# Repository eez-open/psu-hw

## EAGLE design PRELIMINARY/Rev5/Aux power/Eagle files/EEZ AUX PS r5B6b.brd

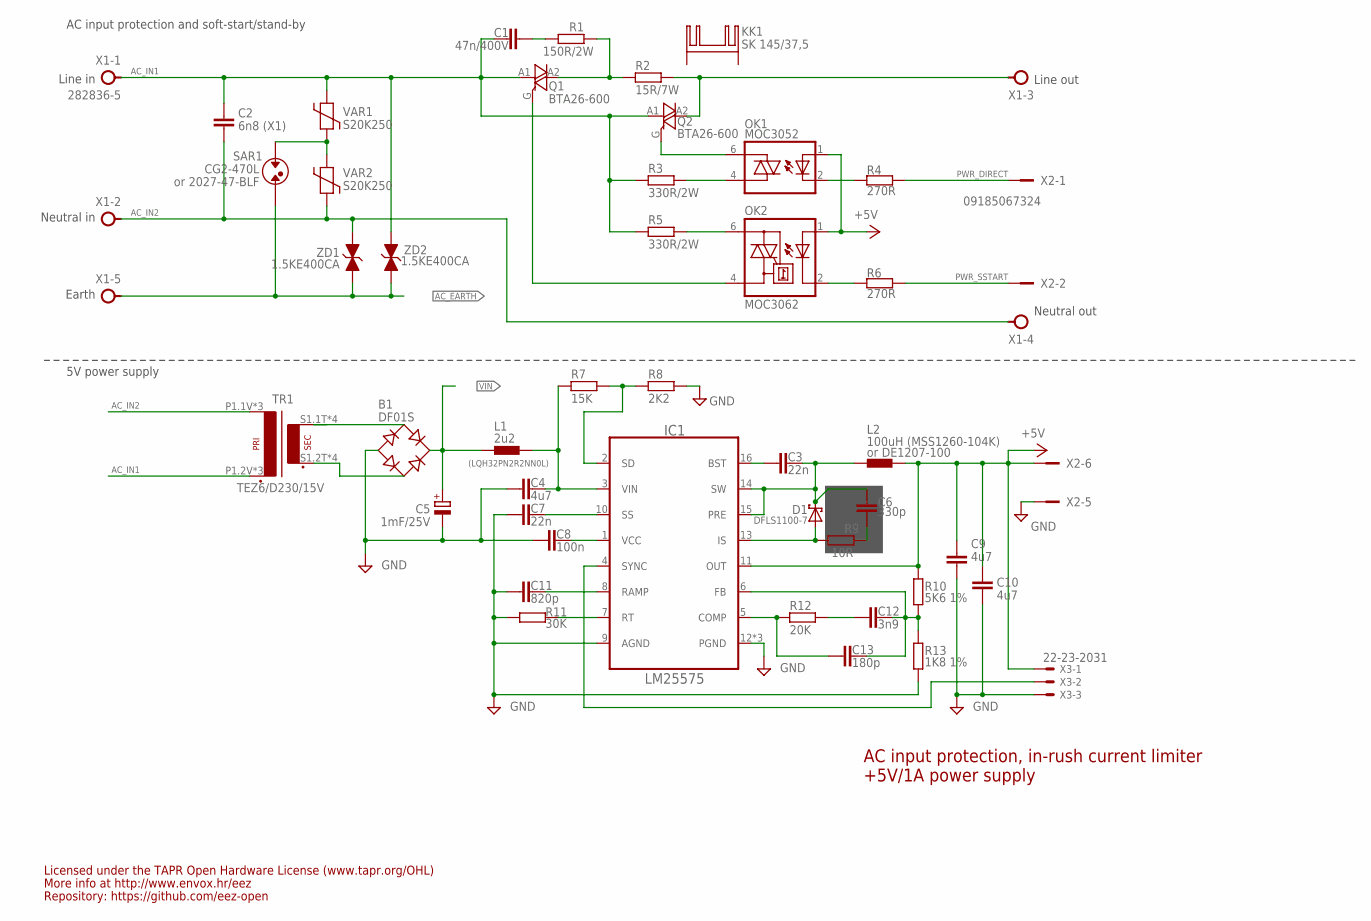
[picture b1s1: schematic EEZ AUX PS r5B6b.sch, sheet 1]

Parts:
B1: DF01S; DFS
C1: 47n/400V; C075-052X106
C2: 6n8 (X1); C102-064X133
C3, C7: 22n; C0805
C4, C9, C10: 4u7; C1210
C5: 1mF/25V; ECAP5/10.5
C6: 330p; C0805
C8: 100n; C0805
C11: 820p; C0805
C12: 3n9; C0805
C13: 180p; C0805
D1: DFLS1100-7; SOD123
IC1: LM25575; SOP65P640X110-17N_HOLE
KK1: SK 145/37,5; SK145
L1: 2u2; L1210
L2: 100uH (MSS1260-104K); MSS1278
OK1: MOC3052; DIL6-SMD
OK2: MOC3062; DIL6-SMD; MPN MOC3033S-M
Q1, Q2: BTA26-600; TOP3S-1
R1: 150R/2W; R2512
R2: 15R/7W; R_0913
R3, R5: 330R/2W; R2512
R4, R6: 270R; R0805
R7: 15K; R0805
R8: 2K2; R0805
R9: 10R; R1206
R10: 5K6 1%; R0805
R11: 30K; R0805
R12: 20K; R0805
R13: 1K8 1%; R0805
SAR1: CG2-470L; SAR
TR1: TEZ6/D230/15V; PCB_TRAFO6VA_TEZ+VPP
VAR1, VAR2: S20K250; VARISTOR
X1: 282836-5; TBLOCK5.0_5
X2: 09185067324; IDC-6PIN
X3: 22-23-2031
ZD1, ZD2: 1.5KE400CA; DO201-BIDIR

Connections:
+5V: C9.1, C10.1, IC1.11 (OUT), L2.2, OK1.1 (A), OK2.1 (A), R10.1, X2.6, X3.1; also elsewhere on the board
AC_EARTH: SAR1.P$2, X1.5, ZD1.C (1), ZD2.C (1); also elsewhere on the board
AC_IN1: C1.2, C2.1, Q1.A1, Q2.A1, R3.2, R5.2, TR1.P1.2V (P2), TR1.P2.2V (P2), TR1.P2_TEZ (P2), VAR1.P$2, X1.1, ZD2.A (2)
AC_IN2: C2.2, TR1.P1.1V (P1), TR1.P1_TEZ (P1), TR1.P2.1V (P1), VAR2.P$1, X1.2, X1.4, ZD1.A (2)
DC_PREG1: C4.1, IC1.3 (VIN), L1.2, R7.2
GND: B1.-, C4.2, C5.-, C7.2, C8.1, C9.2, C10.2, C11.1, IC1.9 (AGND), IC1.12 (PGND), IC1.TP (PGND), IC1.TP2 (PGND), R8.1, R11.2, R13.2, X2.5, X3.3; also elsewhere on the board
IS: D1.A, IC1.13 (IS), R9.1
unnamed: C6.2, R9.2
unnamed: OK1.6 (A2), Q2.G
unnamed: OK1.4 (A1), R3.1
unnamed: OK2.4 (A1), Q1.G
unnamed: OK1.2 (C), R4.1
unnamed: OK2.2 (C), R6.1
unnamed: OK2.6 (A2), R5.1
unnamed: Q2.A2, R2.2, X1.3
unnamed: B1.AC1, TR1.S1.1T (S1), TR1.S1.1V (S1), TR1.S2.1T (S1), TR1.S2.1V (S1)
unnamed: IC1.4 (SYNC), X3.2
unnamed: C1.1, R1.1
unnamed: B1.AC2, TR1.S1.2T (S2), TR1.S1.2V (S2), TR1.S2.2T (S2), TR1.S2.2V (S2)
unnamed: Q1.A2, R1.2, R2.1
unnamed: C12.2, R12.2
unnamed: SAR1.P$1, VAR1.P$1, VAR2.P$2
unnamed: C12.1, C13.1, IC1.6 (FB), R10.2, R13.1
unnamed: C3.2, IC1.16 (BST)
unnamed: C13.2, IC1.5 (COMP), R12.1
unnamed: IC1.7 (RT), R11.1
unnamed: C8.2, IC1.1 (VCC)
unnamed: C11.2, IC1.8 (RAMP)
unnamed: C7.1, IC1.10 (SS)
unnamed: IC1.2 (SD), R7.1, R8.2
PWR_DIRECT: R4.2, X2.1
PWR_SSTART: R6.2, X2.2
SW: C3.1, C6.1, D1.C, IC1.14 (SW), IC1.15 (PRE), L2.1
VIN: B1.+, C5.+, L1.1; also elsewhere on the board

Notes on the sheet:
AC input protection, in-rush current limiter
+5V/1A power supply
Line in
Neutral in
Earth
or DE1207-100
Line out
Neutral out
or 2027-47-BLF
(LQH32PN2R2NN0L)
Licensed under the TAPR Open Hardware License (www.tapr.org/OHL)
Repository: https://github.com/eez-open
More info at http://www.envox.hr/eez
5V power supply
AC input protection and soft-start/stand-by

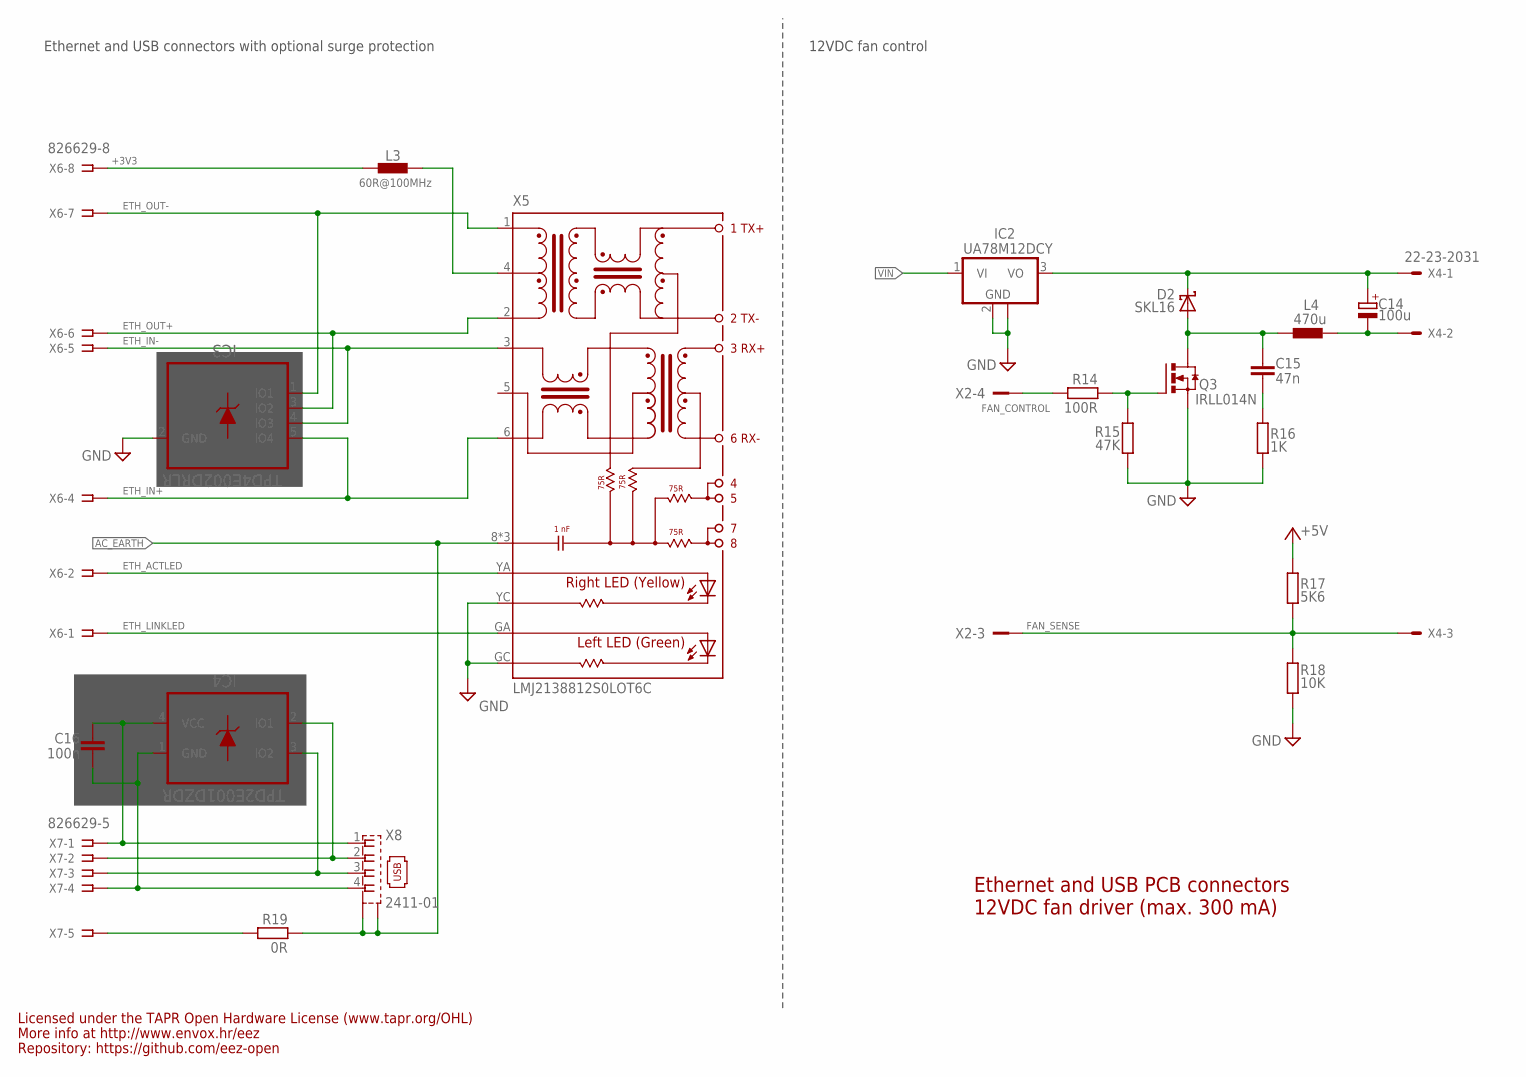
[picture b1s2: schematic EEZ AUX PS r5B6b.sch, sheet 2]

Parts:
C14: 100u; CAPAE660X610N
C15: 47n; C0805
C16: 100n; C0805
D2: SKL16; SOD123
IC2: UA78M12DCY; SOT230P700X180-4N
IC3: TPD4E002DRLR; SOT50P280X60-5N
IC4: TPD2E001DZDR; SOP192P292X122-4N
L3: 60R@100MHz; BEAD0603
L4: 470u; DE0704
Q3: IRLL014N; SOT223
R14: 100R; R0805
R15: 47K; R0805
R16: 1K; R0805
R17: 5K6; R0805
R18: 10K; R0805
R19: 0R; R0805
X2: 09185067324; IDC-6PIN
X4: 22-23-2031
X5: LMJ2138812S0LOT6C; RJ45-VERT
X6: 826629-8; SSW-108-02-S-S
X7: 826629-5; SSW-105-02-S-S
X8: 2411-01; KUSBVX-BS1N

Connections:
+3V3: L3.P$2 (2), X6.8
+5V: R17.1; also elsewhere on the board
AC_EARTH: R19.1, X5.8 (SH), X5.SH1 (SH), X5.SH2 (SH), X8.M1 (S1), X8.M2 (S2); also elsewhere on the board
ETH_ACTLED: X5.YA (YELLOW_A), X6.2
ETH_IN+: IC3.5 (IO4), X5.6 (RD-), X6.4
ETH_IN-: IC3.4 (IO3), X5.3 (RD+), X6.5
ETH_LINKLED: X5.GA (GREEN-A), X6.1
ETH_OUT+: IC3.3 (IO2), X5.2 (TD-), X6.6
ETH_OUT-: IC3.1 (IO1), X5.1 (TD+), X6.7
FAN_CONTROL: R14.2, X2.4
FAN_OUT: C15.2, D2.A, L4.2, Q3.2 (D), Q3.4 (D)
FAN_SENSE: R17.2, R18.1, X2.3, X4.3
GND: IC2.2 (GND), IC2.4 (GND), IC3.2 (GND), Q3.3 (S), R15.1, R16.1, R18.2, X5.GC (GREEN-C), X5.YC (YELLOW-C); also elsewhere on the board
unnamed: C16.2, IC4.4 (VCC), X7.1, X8.1
unnamed: C15.1, R16.2
unnamed: R19.2, X7.5
unnamed: Q3.1 (G), R14.1, R15.2
unnamed: IC4.2 (IO1), X7.2, X8.2
unnamed: C14.1 (+), D2.C, IC2.3 (VO), X4.1
unnamed: C14.2 (-), L4.1, X4.2
unnamed: IC4.3 (IO2), X7.3, X8.3
unnamed: C16.1, IC4.1 (GND), X7.4, X8.4
unnamed: L3.P$1 (1), X5.4 (CT)
VIN: IC2.1 (VI); also elsewhere on the board

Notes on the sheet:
Ethernet and USB PCB connectors
12VDC fan driver (max. 300 mA)
Licensed under the TAPR Open Hardware License (www.tapr.org/OHL)
Repository: https://github.com/eez-open
More info at http://www.envox.hr/eez
Ethernet and USB connectors with optional surge protection
12VDC fan control

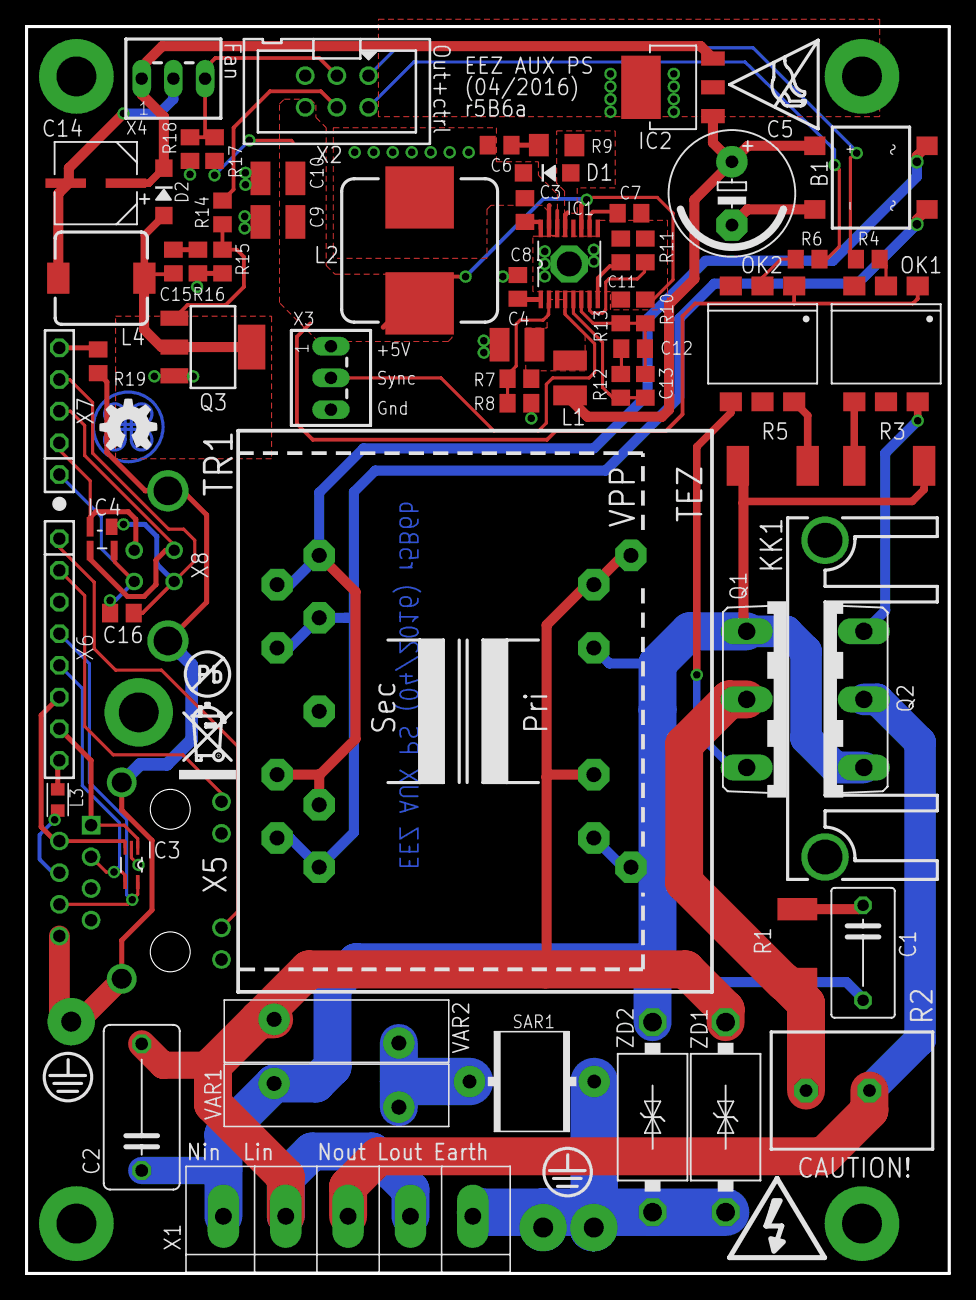
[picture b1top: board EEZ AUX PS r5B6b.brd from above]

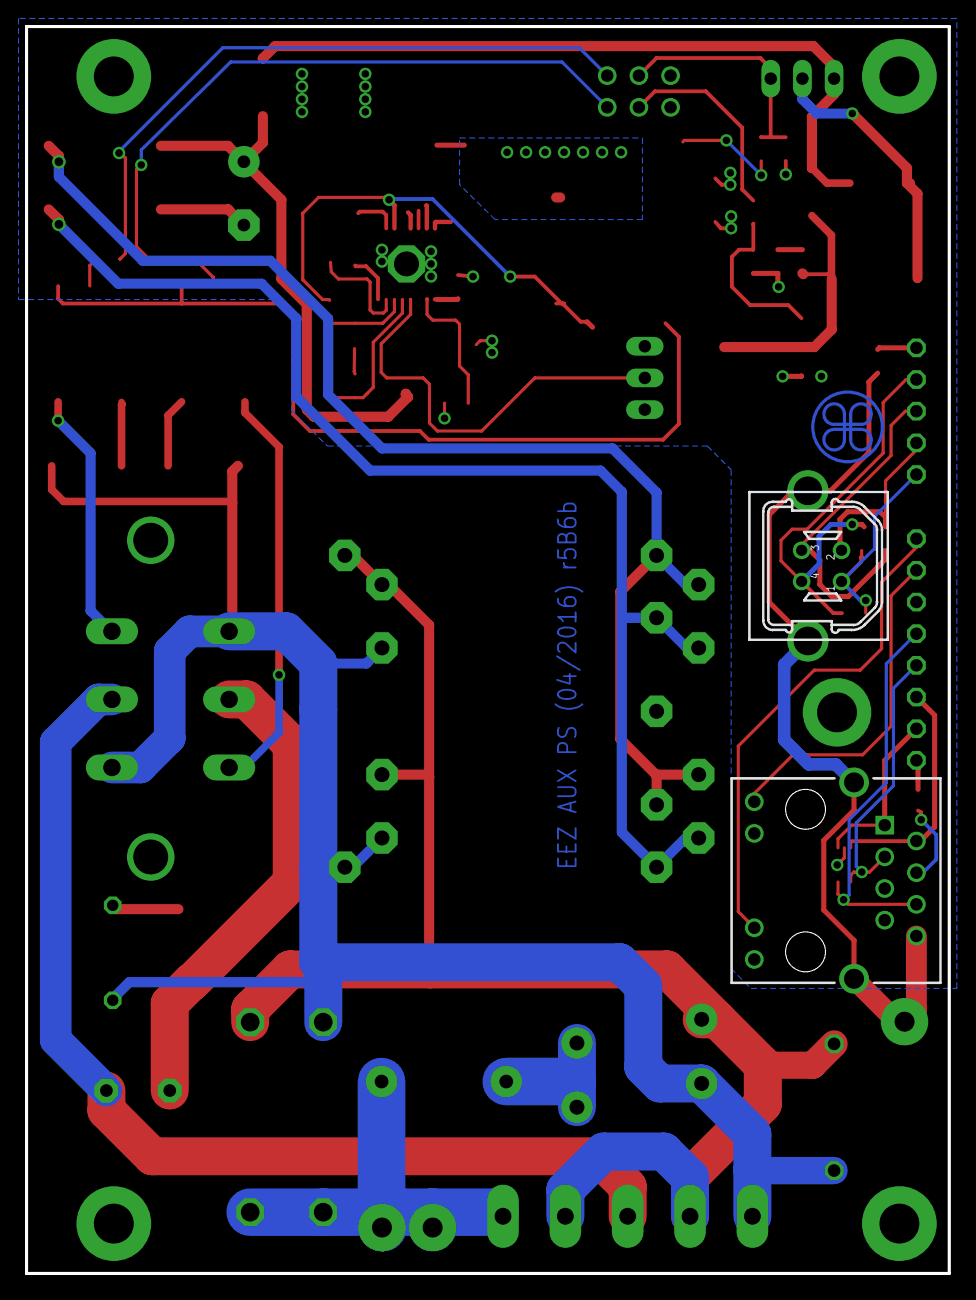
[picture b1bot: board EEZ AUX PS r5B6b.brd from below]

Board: 3 copper layers, 74.0 x 100.0 mm, 70 parts (2 on the bottom side), 54 nets.

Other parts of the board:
EEZ_SIGNATURE: SIGNATURESMALL; SIGNATURE_5MM
U$2: RECYCLE_BIN1/8
U$3: PB_SMALL
U$4: ESD_SYMBOL

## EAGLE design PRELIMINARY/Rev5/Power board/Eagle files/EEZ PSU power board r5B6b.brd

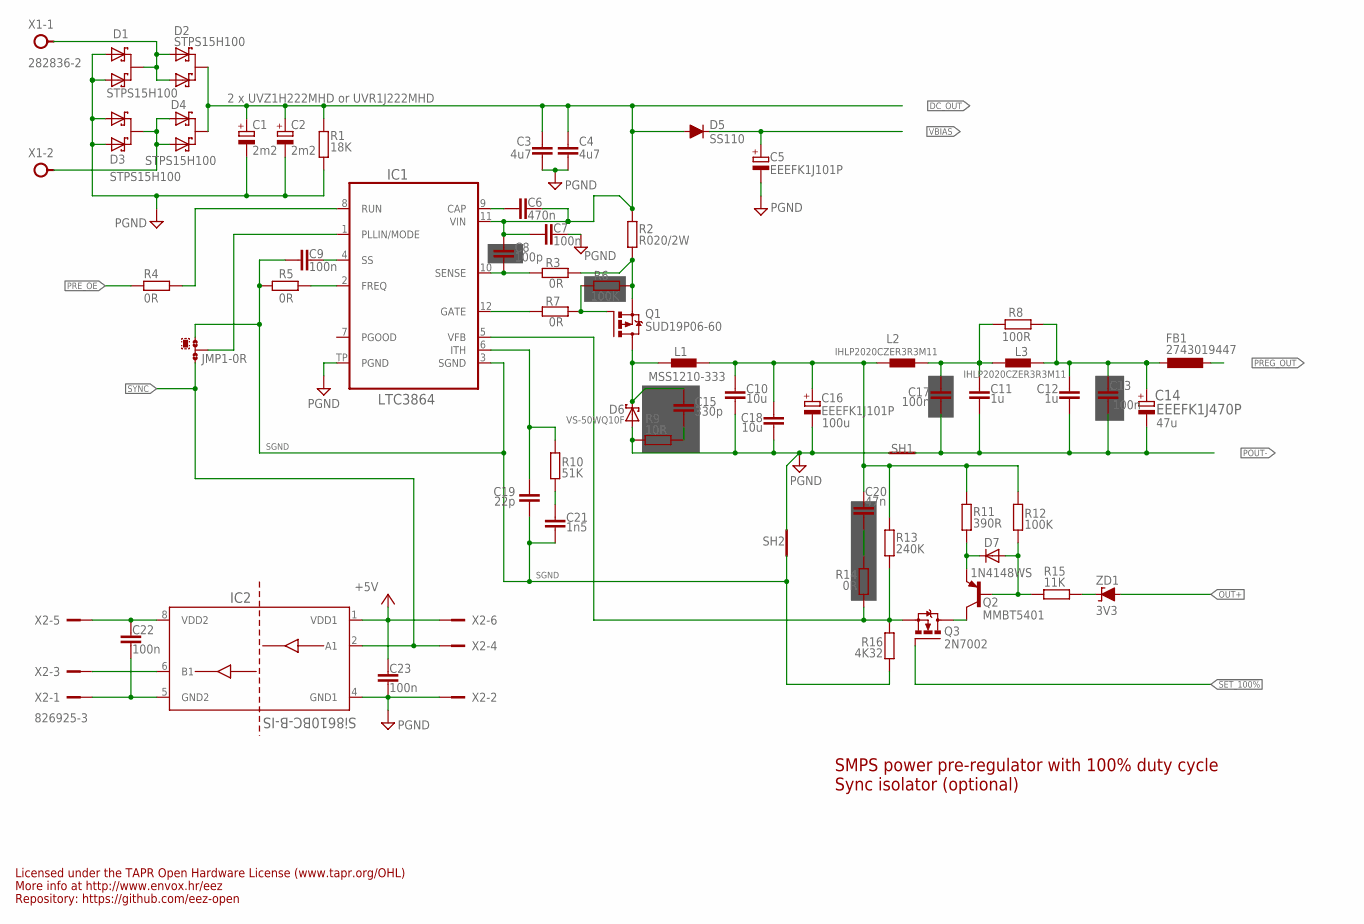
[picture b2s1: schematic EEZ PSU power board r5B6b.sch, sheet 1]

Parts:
C1, C2: 2m2; ECAP7.5/18
C3, C4: 4u7; C1210
C5, C16: EEEFK1J101P; ECAP5/10.5+PANASONIC_F
C6: 470n; C0805
C7, C9, C13, C17: 100n; C0805
C8: 100p; C0805
C10, C18: 10u; C1210
C11, C12: 1u; C1206
C14: EEEFK1J470P; CAPAE830X1050N
C15: 330p; C0805
C19: 22p; C0805
C20: 47n; C0805
C21: 1n5; C0805
C22, C23: 100n; C0603
D1, D2, D3, D4: STPS15H100; TO252@1
D5: SS110; DO214AA
D6: VS-50WQ10F; TO252@1
D7: 1N4148WS; SOD323-W
FB1: 2743019447; L1812
IC1: LTC3864; LTC_05-08-1666
IC2: Si8610BC-B-IS; SOIC127P600X173-8N
JMP1: 0R-JUMPA; A0R-JMP
L1: MSS1210-333; MSS1210
L2, L3: IHLP2020CZER3R3M11; IHLP-2020BZ-11
Q1: SUD19P06-60; TO229P990X239-3N
Q2: MMBT5401; SOT23-BEC
Q3: 2N7002; SOT103P240X110-3N
R1: 18K; R1206
R2: R020/2W; R2512
R3, R4, R5, R7, R14: 0R; R0805
R6, R12: 100K; R0805
R8: 100R; R0805
R9: 10R; R1206
R10: 51K; R0805
R11: 390R; R0805
R13: 240K; R0805
R15: 11K; R0805
R16: 4K32; R0805
SH1: Pgnd to Pout- short; SHORT
SH2: Sgnd to Pgnd short; SHORT
X1: 282836-2; TBLOCK5.0_2
X2: 826925-3; TSW-103-07-F-D
ZD1: 3V3; MINIMELF

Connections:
!SET_100%: Q3.1 (G); also elsewhere on the board
+5V: C23.1, IC2.1 (VDD1), X2.6; also elsewhere on the board
AC_IN1: D3.3 (C), D4.1 (A1), D4.2 (A2), X1.2
AC_IN2: D1.3 (C), D2.1 (A1), D2.2 (A2), X1.1
DC_OUT: C1.+, C2.+, C3.1, C4.1, C6.2, C7.1, C8.1, D2.3 (C), D4.3 (C), D5.A, IC1.11 (VIN), R1.1, R2.1; also elsewhere on the board
FB: IC1.5 (VFB), Q3.2 (S), R13.2, R14.1, R16.1
GND: C1.-, C2.-, C3.2, C4.2, C5.-, C5.-.1 (-), C7.2, C10.2, C16.-, C16.-.1 (-), C18.2, C23.2, D1.1 (A1), D1.2 (A2), D3.1 (A1), D3.2 (A2), D6.1 (A), D6.2 (A), IC1.TP (PGND), IC2.4 (GND1), R1.2, R9.1, SH1.2 (GND_B), SH2.2 (GND_B), X2.2; also elsewhere on the board
ISO_GND: C22.2, IC2.5 (GND2), X2.1
L_OUT: C10.1, C16.+, C16.+.1 (+), C18.1, C20.1, L1.2, L2.1, R11.1, R12.1, R13.1
MODE: IC1.1 (PLLIN/MODE), JMP1.2
unnamed: C20.2, R14.2
unnamed: D7.C, Q2.E, R11.2
unnamed: C19.1, IC1.6 (ITH), R10.2
unnamed: C21.1, R10.1
unnamed: C6.1, IC1.9 (CAP)
unnamed: C8.2, IC1.10 (SENSE), R3.2
unnamed: R15.2, ZD1.C
unnamed: IC1.12 (GATE), R7.2
unnamed: Q1.1 (G), R6.1, R7.1
unnamed: IC1.2 (FREQ), R5.1
unnamed: C9.2, IC1.4 (SS)
unnamed: Q2.C, Q3.3 (D)
unnamed: C11.1, C17.2, L2.2, L3.1, R8.1
unnamed: IC1.8 (RUN), R4.1
unnamed: C15.2, R9.2
unnamed: D7.A, Q2.B, R12.2, R15.1
unnamed: IC2.6 (B1), X2.3
unnamed: C22.1, IC2.8 (VDD2), X2.5
OUT+: ZD1.A; also elsewhere on the board
POUT-: C11.2, C12.2, C13.2, C14.2, C17.1, SH1.1 (GND_A); also elsewhere on the board
PREG_OUT: FB1.2; also elsewhere on the board
PRE_OE: R4.2; also elsewhere on the board
P_OUT: C12.1, C13.1, C14.1, FB1.1, L3.2, R8.2
SENSE: Q1.3 (S), R2.2, R3.1, R6.2
SGND: C9.1, C19.2, C21.2, IC1.3 (SGND), JMP1.1, R5.2, R16.2, SH2.1 (GND_A)
SW: C15.1, D6.3 (C), L1.1, Q1.2 (D)
SYNC: IC2.2 (A1), JMP1.3, X2.4; also elsewhere on the board
VBIAS: C5.+, C5.+.1 (+), D5.C; also elsewhere on the board

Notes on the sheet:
47u
2 x UVZ1H222MHD or UVR1J222MHD
Licensed under the TAPR Open Hardware License (www.tapr.org/OHL)
Repository: https://github.com/eez-open
More info at http://www.envox.hr/eez
SMPS power pre-regulator with 100% duty cycle
Sync isolator (optional)
100u

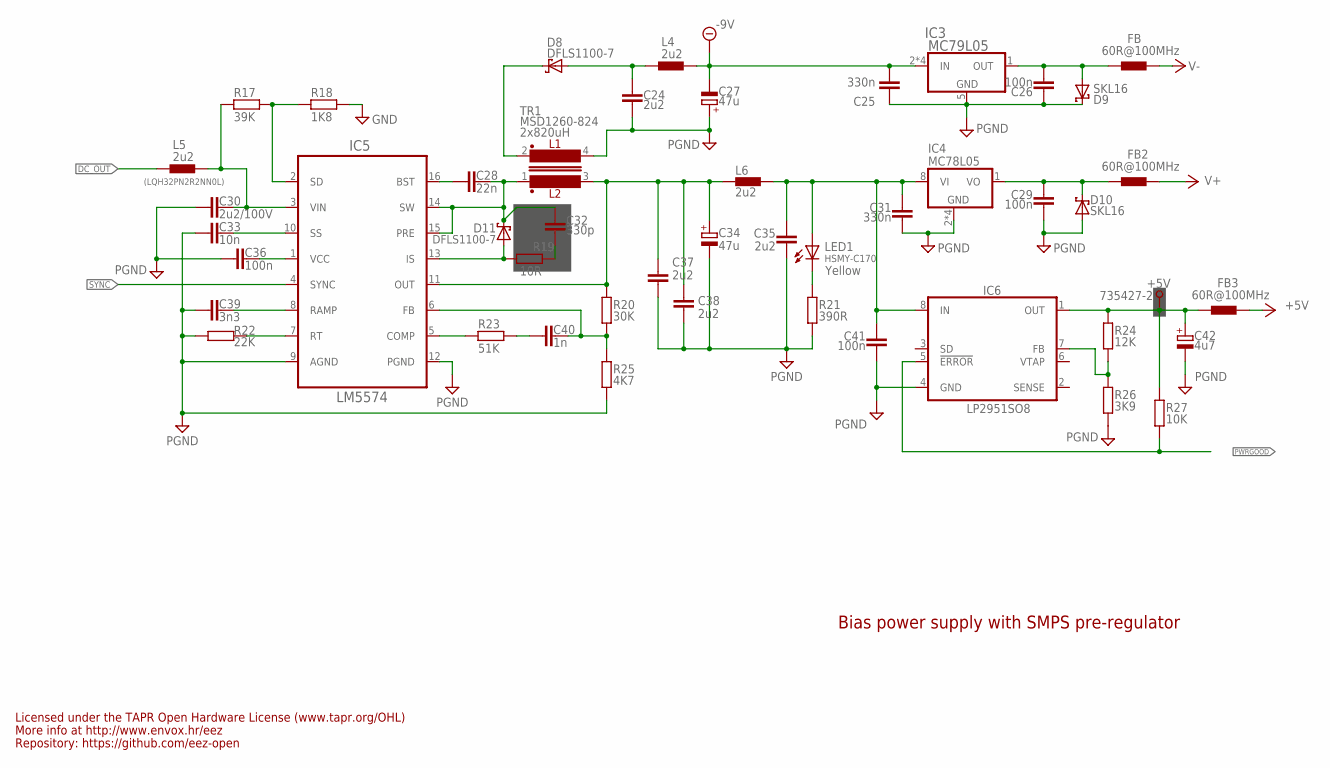
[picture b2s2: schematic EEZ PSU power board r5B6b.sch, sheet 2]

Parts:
+5V: 735427-2; PCB_SHIELD_TAB
C24, C35, C37, C38: 2u2; C0805
C25, C31: 330n; C0805
C26, C29, C36, C41: 100n; C0805
C27, C34: 47u; CAPAE660X610N
C28: 22n; C0805
C30: 2u2/100V; C1210
C32: 330p; C0805
C33: 10n; C0805
C39: 3n3; C0805
C40: 1n; C0805
C42: 4u7; EC1206
D8, D11: DFLS1100-7; SOD123
D9, D10: SKL16; SOD123
FB, FB2, FB3: 60R@100MHz; BEAD0603
IC3: MC79L05; SOIC127P600X173-8N
IC4: MC78L05; SOIC127P600X173-8N
IC5: LM5574; SOP65P640X110-16N
IC6: LP2951SO8; SOIC127P600X175-8N
L4, L5, L6: 2u2; L1210
LED1: HSMY-C170; CHIPLED_0805
R17: 39K; R0805
R18: 1K8; R0805
R19: 10R; R1206
R20: 30K; R0805
R21: 390R; R0805
R22: 22K; R0805
R23: 51K; R0805
R24: 12K; R0805
R25: 4K7; R0805
R26: 3K9; R0805
R27: 10K; R0805
TR1: MSD1260-824; MSD1260

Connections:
+5V: FB3.P$2 (2); also elsewhere on the board
+VNR: C31.1, C35.1, C41.1, IC4.8 (VI), IC6.8 (IN), L6.2, LED1.A
-9V: C25.2, C27.2 (-), IC3.2 (IN), IC3.3 (IN), IC3.6 (IN), IC3.7 (IN), L4.2; also elsewhere on the board
DC_OUT: L5.1; also elsewhere on the board
DC_PREG1: C30.1, IC5.3 (VIN), L5.2, R17.2
GND: C24.2, C25.1, C26.1, C27.1 (+), C29.2, C30.2, C31.2, C33.2, C34.2 (-), C35.2, C36.1, C37.2, C38.2, C39.1, C41.2, C42.-, D9.C, D10.A, IC3.5 (GND), IC4.2 (GND), IC4.3 (GND), IC4.6 (GND), IC4.7 (GND), IC5.9 (AGND), IC5.12 (PGND), IC6.4 (GND), R18.1, R21.2, R22.2, R25.2, R26.2, TR1.4; also elsewhere on the board
IS: D11.A, IC5.13 (IS), R19.1
unnamed: C26.2, D9.A, FB.P$1 (1), IC3.1 (OUT)
unnamed: C29.1, D10.C, FB2.P$1 (1), IC4.1 (VO)
unnamed: +5V.1, C42.+, FB3.P$1 (1), IC6.1 (OUT), R24.1, R27.1
unnamed: LED1.C, R21.1
unnamed: C32.2, R19.2
unnamed: IC6.7 (FB), R24.2, R26.1
unnamed: C40.2, R23.2
unnamed: C40.1, IC5.6 (FB), R20.2, R25.1
unnamed: C28.2, IC5.16 (BST)
unnamed: IC5.5 (COMP), R23.1
unnamed: IC5.7 (RT), R22.1
unnamed: C36.2, IC5.1 (VCC)
unnamed: C39.2, IC5.8 (RAMP)
unnamed: C33.1, IC5.10 (SS)
unnamed: C24.1, D8.A, L4.1
unnamed: IC5.2 (SD), R17.1, R18.2
PWRGOOD: IC6.5 (!ERROR), R27.2; also elsewhere on the board
SW1: C28.1, C32.1, D11.C, IC5.14 (SW), IC5.15 (PRE), TR1.1
SYNC: IC5.4 (SYNC); also elsewhere on the board
V+: FB2.P$2 (2); also elsewhere on the board
V-: FB.P$2 (2); also elsewhere on the board
VOUT+: C34.1 (+), C37.1, C38.1, IC5.11 (OUT), L6.1, R20.1, TR1.3
VOUT-: D8.C, TR1.2

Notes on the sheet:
2x820uH
(LQH32PN2R2NN0L)
Bias power supply with SMPS pre-regulator
Yellow
Licensed under the TAPR Open Hardware License (www.tapr.org/OHL)
Repository: https://github.com/eez-open
More info at http://www.envox.hr/eez

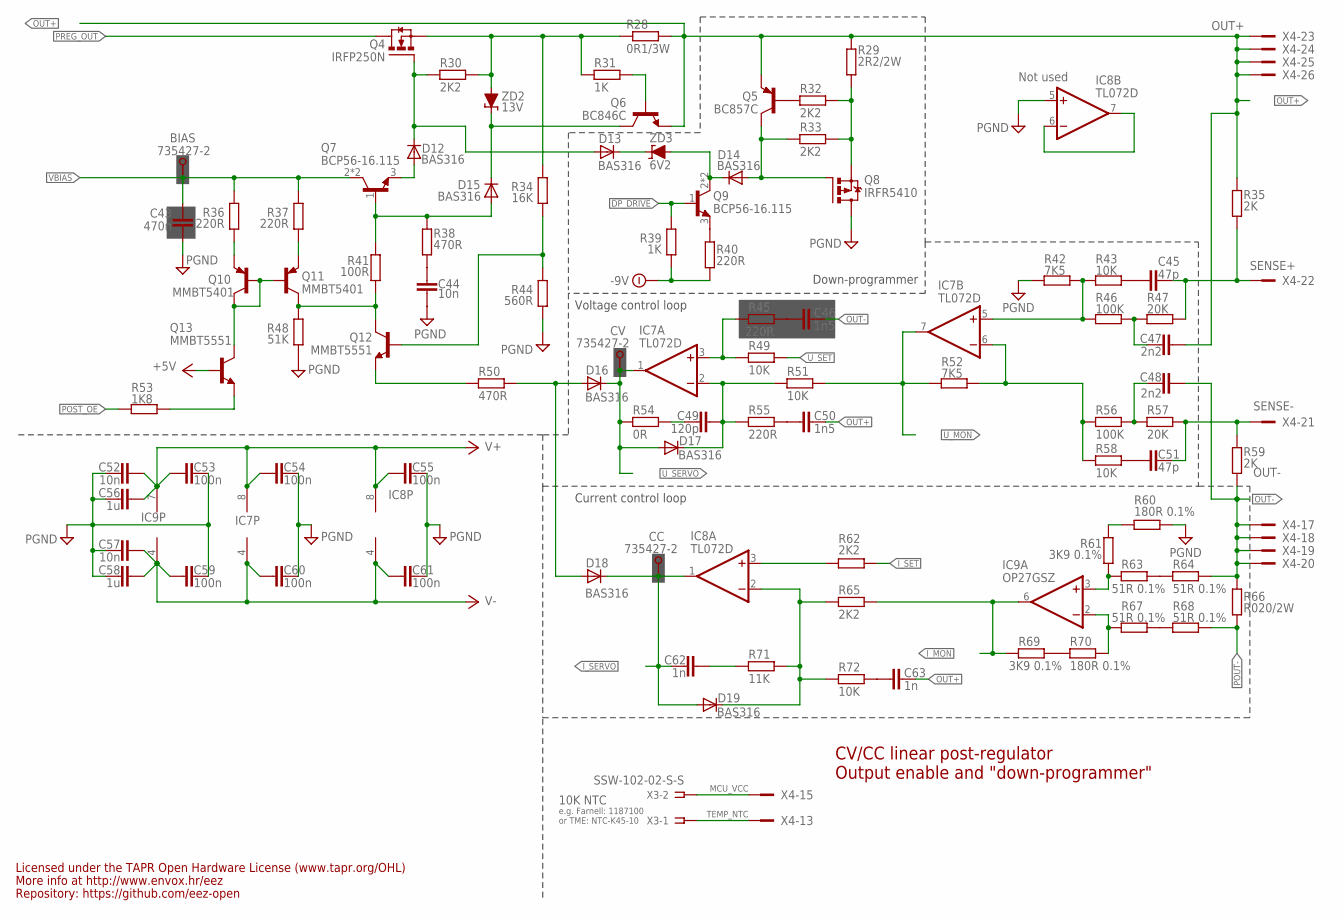
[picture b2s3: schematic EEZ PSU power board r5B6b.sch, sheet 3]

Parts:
BIAS: 735427-2; PCB_SHIELD_TAB
C43: 470n; C1812
C44, C52, C57: 10n; C0805
C45, C51: 47p; C0805
C46, C50: 1n5; C0805
C47, C48: 2n2; C0805
C49: 120p; C0805
C53, C54, C55, C59, C60, C61: 100n; C0603
C56, C58: 1u; C0805
C62, C63: 1n; C0805
CC: 735427-2; PCB_SHIELD_TAB
CV: 735427-2; PCB_SHIELD_TAB
D12, D13, D14, D15, D16, D17, D18, D19: BAS316; SOD323-W
IC7, IC8: TL072D; SOIC127P600X173-8N
IC9: OP27GSZ; SOIC127P600X173-8N
Q4: IRFP250N; TO247BH-CLR
Q5: BC857C; SOT23-BEC
Q6: BC846C; SOT23-BEC
Q7, Q9: BCP56-16.115; SOT230P700X180-4N
Q8: IRFR5410; TO229P990X239-3N
Q10, Q11: MMBT5401; SOT23-BEC
Q12, Q13: MMBT5551; SOT23-BEC
R28: 0R1/3W; R_2512+0411/15
R29: 2R2/2W; R_2512+0411/15
R30, R32, R33, R62, R65: 2K2; R0805
R31, R39: 1K; R0805
R34: 16K; R0805
R35, R59: 2K; R0805
R36, R37, R40, R45, R55: 220R; R0805
R38, R50: 470R; R0805
R41: 100R; R0805
R42, R52: 7K5; R0805
R43, R49, R51, R58, R72: 10K; R0805
R44: 560R; R0805
R46, R56: 100K; R0805
R47, R57: 20K; R0805
R48: 51K; R0805
R53: 1K8; R0805
R54: 0R; R0805
R60, R70: 180R 0.1%; R0805
R61, R69: 3K9 0.1%; R0805
R63, R64, R67, R68: 51R 0.1%; R0805
R66: R020/2W; R2512
R71: 11K; R0805
X3: SSW-102-02-S-S
X4: SSW-113-02-T-D-RA; FARNELL 1805583
ZD2: 13V; MINIMELF
ZD3: 6V2; MINIMELF

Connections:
!DP_DRIVE: Q9.1 (B), R39.1; also elsewhere on the board
+5V: Q13.B; also elsewhere on the board
-9V: R39.2, R40.2; also elsewhere on the board
GND: C43.2, C44.2, C52.1, C53.2, C54.1, C55.1, C56.1, C57.1, C58.1, C59.2, C60.1, C61.1, IC8.5 (+IN), Q8.2 (D), R42.1, R44.1, R48.1, R60.1; also elsewhere on the board
ISENSE+: IC9.3 (+IN), R61.2, R63.2
ISENSE-: IC9.2 (-IN), R67.2, R70.1
I_MON: IC9.6 (OUT), R65.1, R69.2; also elsewhere on the board
I_SERVO: C62.2, CC.1, D18.C, D19.A, IC8.1 (OUT); also elsewhere on the board
I_SET: R62.1; also elsewhere on the board
MCU_VCC: X3.2, X4.15
unnamed: Q9.3 (E), R40.1
unnamed: Q5.B, R32.2
unnamed: C45.2, R43.1
unnamed: R63.1, R64.2
unnamed: C51.2, R58.1
unnamed: R67.1, R68.2
unnamed: R69.1, R70.2
unnamed: R60.2, R61.1
unnamed: IC8.6 (-IN), IC8.7 (OUT)
unnamed: C48.1, R56.2, R57.1
unnamed: C49.2, R54.1
unnamed: C63.2, R72.1
unnamed: C46.2, R45.1
unnamed: C50.2, R55.1
unnamed: IC7.3 (+IN), R45.2, R49.2
unnamed: C49.1, D17.C, IC7.2 (-IN), R51.2, R55.2
unnamed: D19.C, IC8.2 (-IN), R65.2, R71.2, R72.2
unnamed: Q12.B, R34.1, R44.2
unnamed: IC8.3 (+IN), R62.2
unnamed: D16.A, D18.A, R50.1
unnamed: D12.C, D13.A, Q4.G, R30.1
unnamed: D12.A, Q7.3 (E)
unnamed: D15.A, Q7.1 (B), R38.2, R41.1
unnamed: C44.1, R38.1
unnamed: C47.1, R46.2, R47.1
unnamed: D15.C, Q6.C, ZD2.C
unnamed: D13.C, ZD3.C
unnamed: Q12.E, R50.2
unnamed: Q8.3 (S), R29.1, R29.1.1 (1), R32.1, R33.1
unnamed: D14.A, Q5.C, Q8.1 (G), R33.2
unnamed: IC7.5 (+IN), R42.2, R43.2, R46.1
unnamed: IC7.6 (-IN), R52.2, R56.1, R58.2
unnamed: C62.1, R71.1
unnamed: Q11.E, R37.1
unnamed: Q10.E, R36.1
unnamed: Q13.E, R53.2
unnamed: Q6.B, R31.1
OUT+: C47.2, C50.1, C63.1, Q5.E, Q6.E, R28.2, R28.2.1 (2), R29.2, R29.2.1 (2), R35.1, X4.23, X4.24, X4.25, X4.26; also elsewhere on the board
OUT-: C46.1, C48.2, R59.2, R64.1, R66.1, X4.17, X4.18, X4.19, X4.20
POST_OE: R53.1; also elsewhere on the board
POUT-: R66.2, R68.1; also elsewhere on the board
PREG_OUT: Q4.D; also elsewhere on the board
Q4_OUT: Q4.S, R28.1, R28.1.1 (1), R30.2, R31.2, R34.2, ZD2.A
Q7C: Q10.B, Q10.C, Q11.B, Q13.C
Q9C: D14.C, Q9.2 (C), Q9.4 (C), ZD3.A
Q11C: Q11.C, Q12.C, R41.2, R48.2
SENSE+: C45.1, R35.2, R47.2, X4.22
SENSE-: C51.1, R57.2, R59.1, X4.21
TEMP_NTC: X3.1, X4.13
U_MON: IC7.7 (OUT), R51.1, R52.1; also elsewhere on the board
U_SERVO: CV.1, D16.C, D17.A, IC7.1 (OUT), R54.2; also elsewhere on the board
U_SET: R49.1; also elsewhere on the board
V+: C52.2, C53.1, C54.2, C55.2, C56.2, IC7.8 (V+), IC8.8 (V+), IC9.7 (V+); also elsewhere on the board
V-: C57.2, C58.2, C59.1, C60.2, C61.2, IC7.4 (V-), IC8.4 (V-), IC9.4 (V-); also elsewhere on the board
VBIAS: BIAS.1, C43.1, Q7.2 (C), Q7.4 (C), R36.2, R37.2; also elsewhere on the board

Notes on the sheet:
Current control loop
Voltage control loop
CV/CC linear post-regulator
Output enable and "down-programmer"
Down-programmer
Not used
e.g. Farnell: 1187100
10K NTC
or TME: NTC-K45-10
Licensed under the TAPR Open Hardware License (www.tapr.org/OHL)
Repository: https://github.com/eez-open
More info at http://www.envox.hr/eez

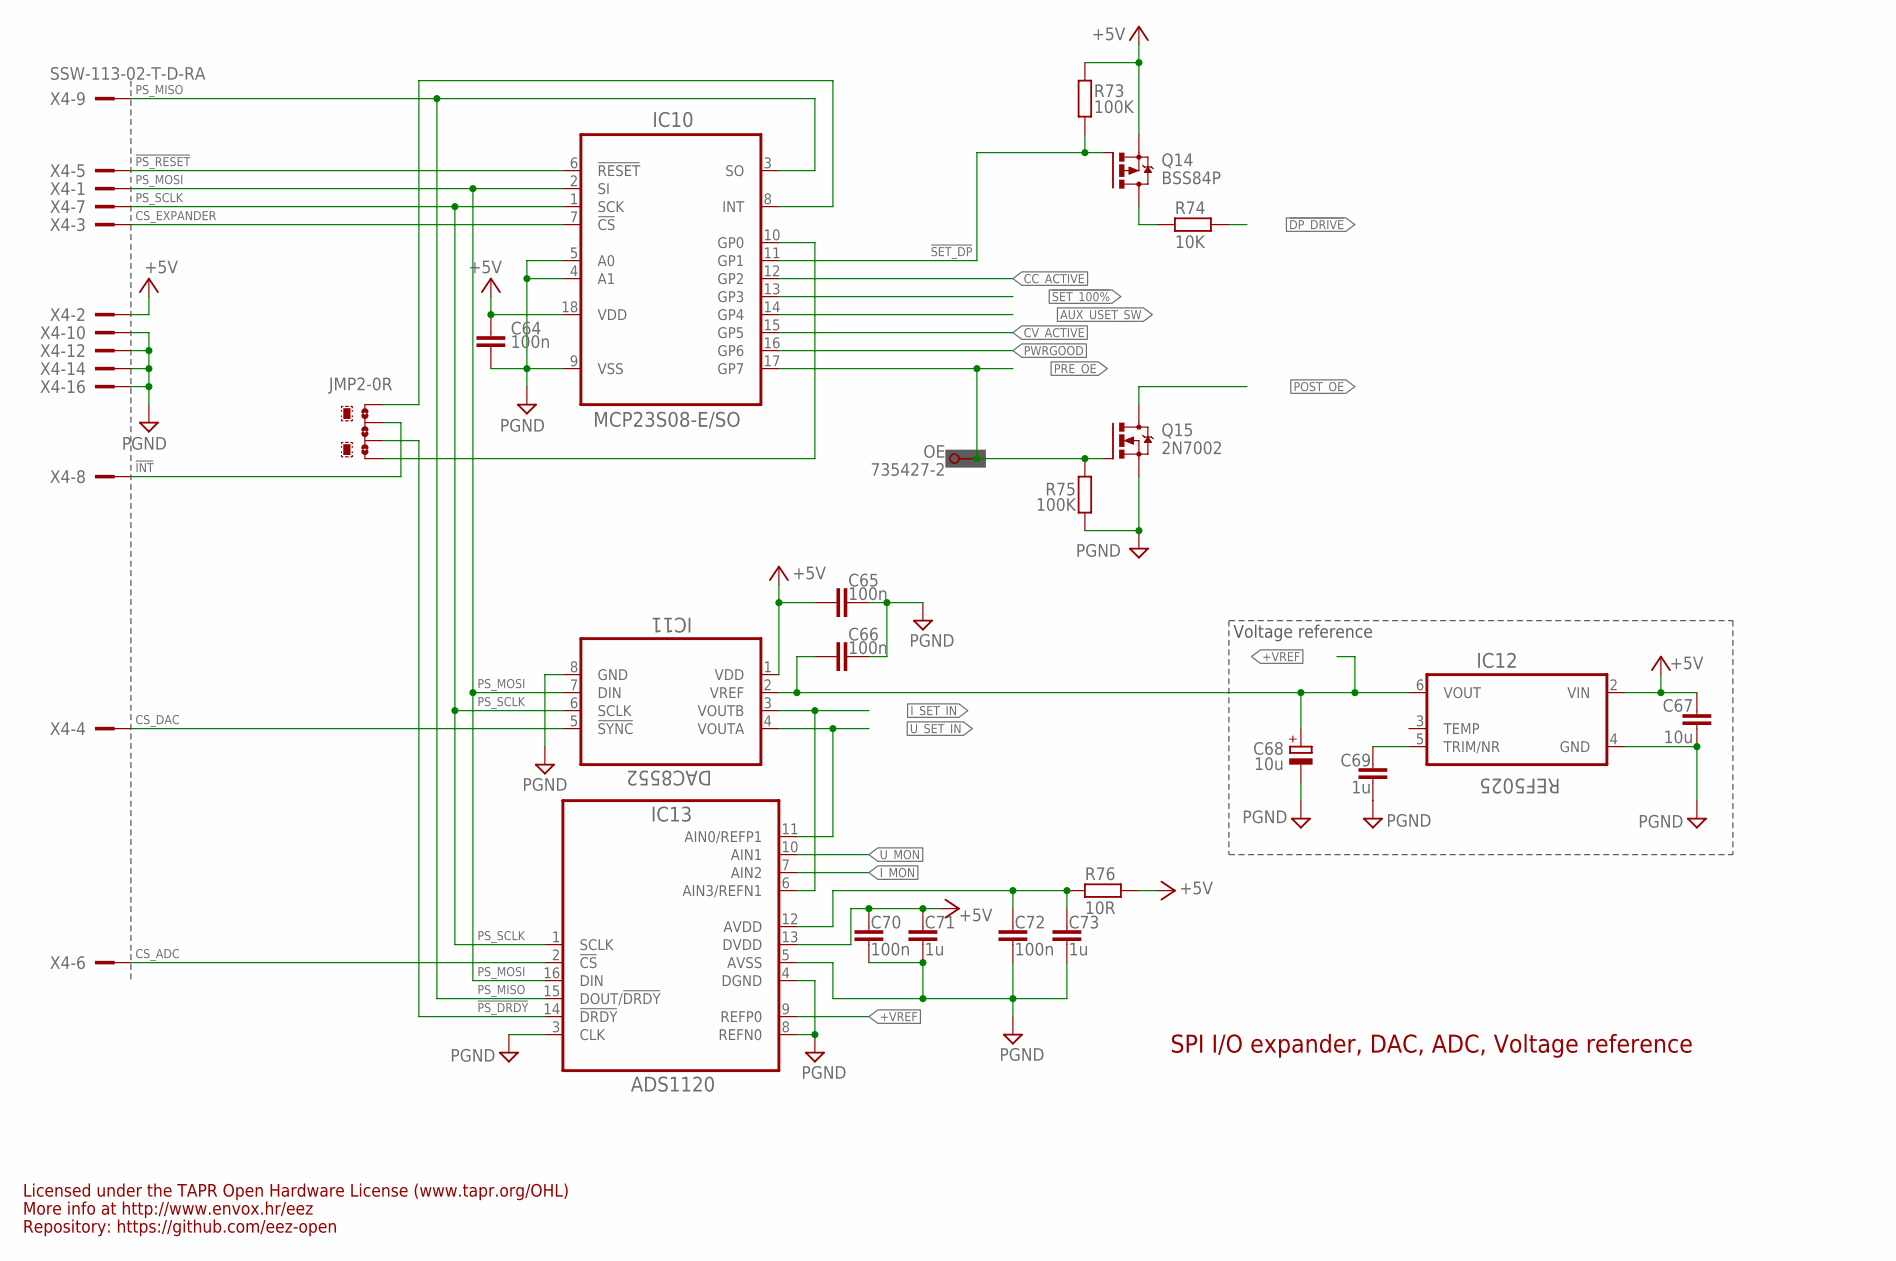
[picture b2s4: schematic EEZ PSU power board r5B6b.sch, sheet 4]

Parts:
C64, C65, C66, C70, C72: 100n; C0603
C67: 10u; C1206
C68: 10u; EC1206
C69, C71, C73: 1u; C0805
IC10: MCP23S08-E/SO; SOIC127P1030X265-18N
IC11: DAC8552; DGK8-M
IC12: REF5025; SOIC127P600X175-8N
IC13: ADS1120; PW(R-PDSO-G16)
JMP2: 0R-JMP41-2,3-4; 0R-JMP4
OE: 735427-2; PCB_SHIELD_TAB
Q14: BSS84P; SOT95P237X112-3N
Q15: 2N7002; SOT103P240X110-3N; MPN 2N7002-7-F
R73, R75: 100K; R0805
R74: 10K; R0805
R76: 10R; R0805
X4: SSW-113-02-T-D-RA; FARNELL 1805583

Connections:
!DP_DRIVE: R74.1; also elsewhere on the board
!INT: JMP2.3, X4.8
!PS_DRDY: IC13.14 (!DRDY), JMP2.2
!PS_RESET: IC10.6 (!RESET), X4.5
!SET_100%: IC10.13 (GP3); also elsewhere on the board
!SET_DP: IC10.11 (GP1), Q14.1 (G), R73.2
+5V: C64.1, C65.2, C67.1, C70.2, C71.2, IC10.18 (VDD), IC11.1 (VDD), IC12.2 (VIN), IC13.13 (DVDD), Q14.2 (S), R73.1, R76.1, X4.2; also elsewhere on the board
+VREF: C66.2, C68.+, IC11.2 (VREF), IC12.6 (VOUT), IC13.9 (REFP0); also elsewhere on the board
AUX_USET_SW: IC10.14 (GP4); also elsewhere on the board
CC_ACTIVE: IC10.12 (GP2); also elsewhere on the board
CS_ADC: IC13.2 (!CS), X4.6
CS_DAC: IC11.5 (!SYNC), X4.4
CS_EXPANDER: IC10.7 (!CS), X4.3
CV_ACTIVE: IC10.15 (GP5); also elsewhere on the board
DP_LED: Q14.3 (D), R74.2
GND: C64.2, C65.1, C66.1, C67.2, C68.-, C69.2, C70.1, C71.1, C72.1, C73.1, IC10.4 (A1), IC10.5 (A0), IC10.9 (VSS), IC11.8 (GND), IC12.4 (GND), IC13.3 (CLK), IC13.4 (DGND), IC13.5 (AVSS), IC13.8 (REFN0), Q15.2 (S), R75.1, X4.10, X4.12, X4.14, X4.16; also elsewhere on the board
INT_EXP: IC10.8 (INT), JMP2.4
I_MON: IC13.7 (AIN2); also elsewhere on the board
I_SET_IN: IC11.3 (VOUTB), IC13.6 (AIN3/REFN1); also elsewhere on the board
unnamed: C69.1, IC12.5 (TRIM/NR)
unnamed: C72.2, C73.2, IC13.12 (AVDD), R76.2
unnamed: IC10.10 (GP0), JMP2.1
POST_OE: Q15.3 (D); also elsewhere on the board
PRE_OE: IC10.17 (GP7), OE.1, Q15.1 (G), R75.2; also elsewhere on the board
PS_MISO: IC10.3 (SO), IC13.15 (DOUT/!DRDY), X4.9
PS_MOSI: IC10.2 (SI), IC11.7 (DIN), IC13.16 (DIN), X4.1
PS_SCLK: IC10.1 (SCK), IC11.6 (SCLK), IC13.1 (SCLK), X4.7
PWRGOOD: IC10.16 (GP6); also elsewhere on the board
U_MON: IC13.10 (AIN1); also elsewhere on the board
U_SET_IN: IC11.4 (VOUTA), IC13.11 (AIN0/REFP1); also elsewhere on the board

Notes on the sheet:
SPI I/O expander, DAC, ADC, Voltage reference
Voltage reference
Licensed under the TAPR Open Hardware License (www.tapr.org/OHL)
Repository: https://github.com/eez-open
More info at http://www.envox.hr/eez
